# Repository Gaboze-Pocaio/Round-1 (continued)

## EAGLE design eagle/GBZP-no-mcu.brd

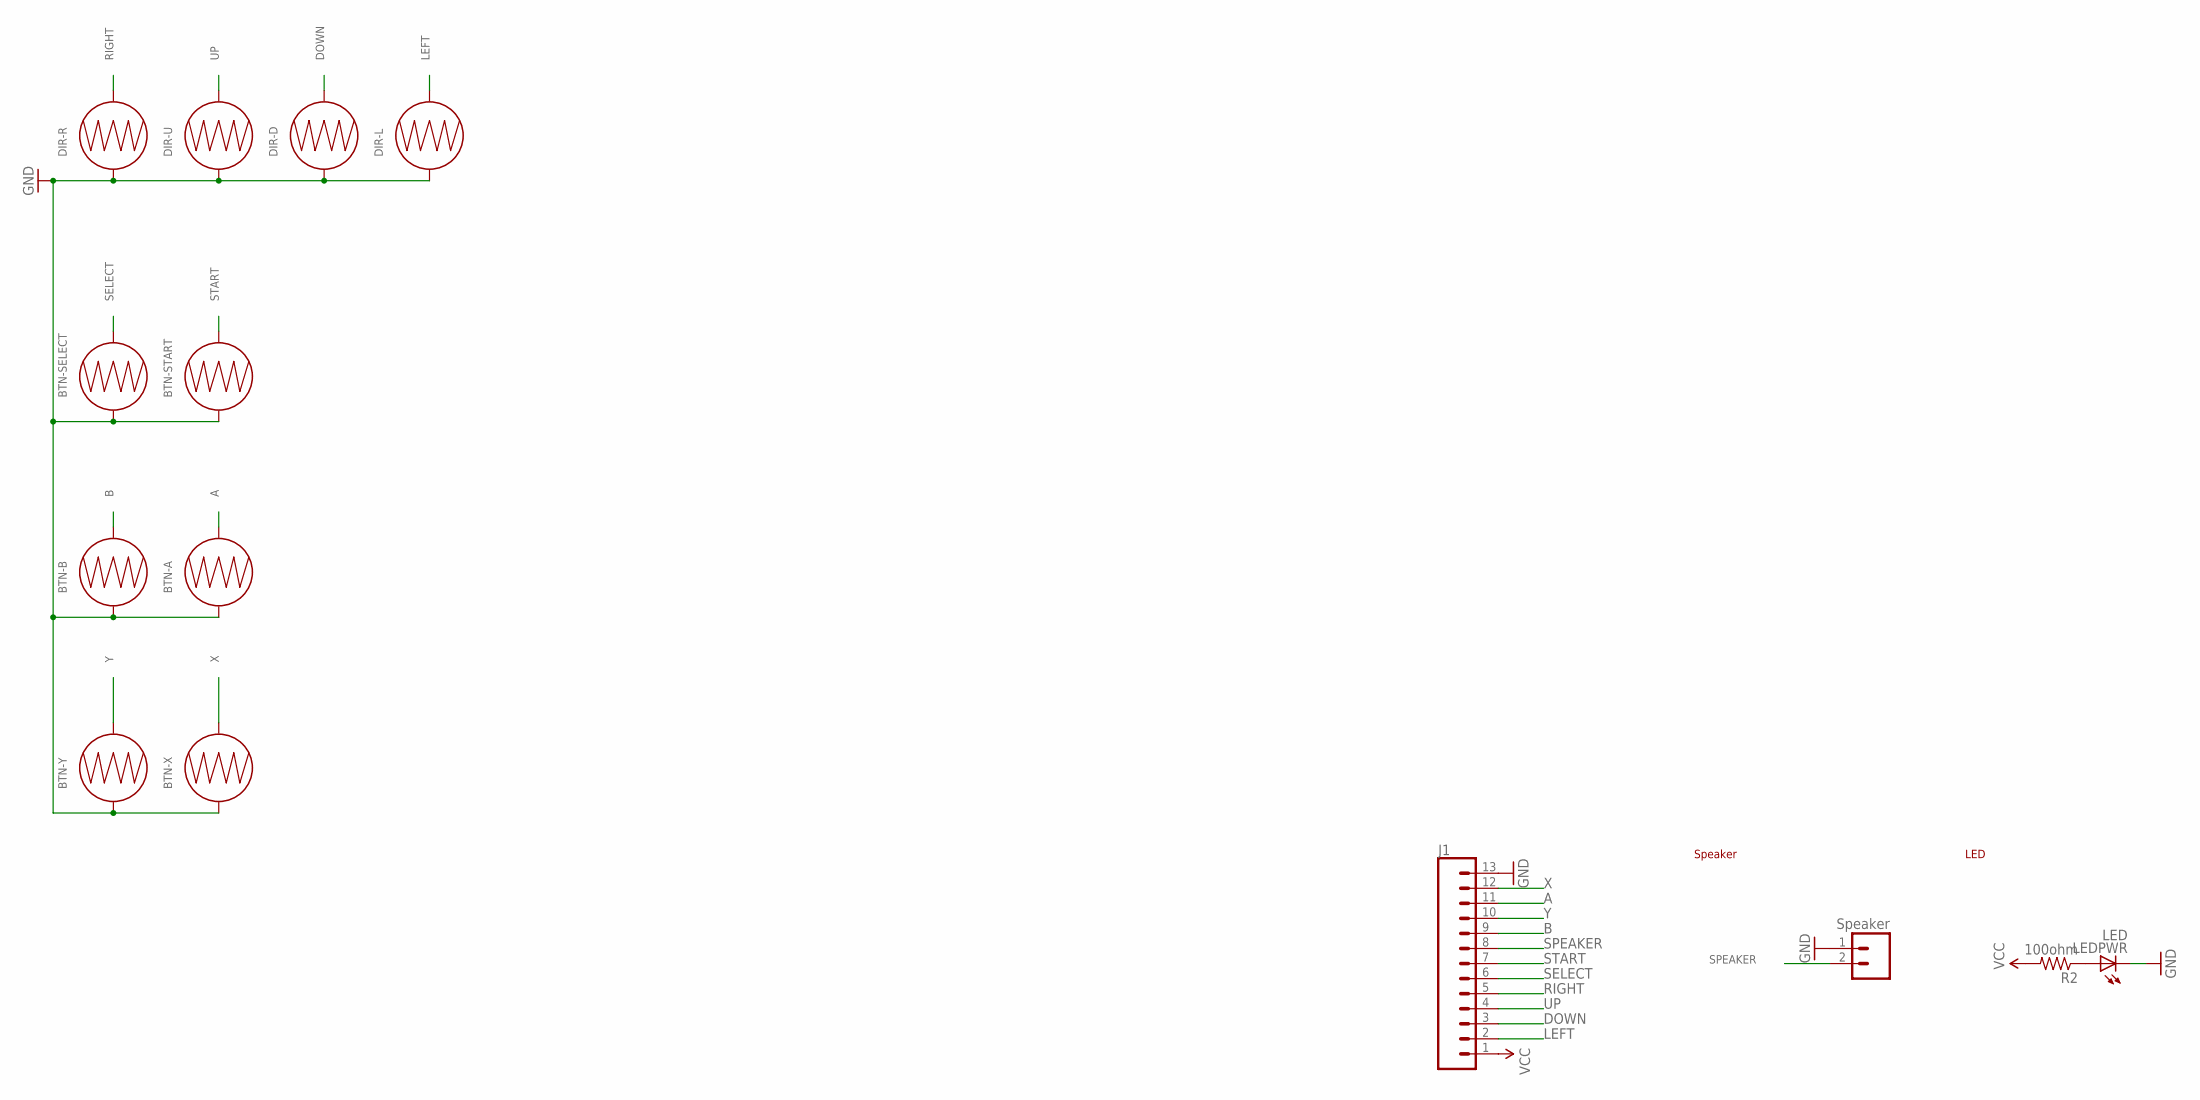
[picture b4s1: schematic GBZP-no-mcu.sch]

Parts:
BTN-A: BUTTON-CONDUCTIVESMD; BUTTON-CONDUCTIVE
BTN-B: BUTTON-CONDUCTIVESMD; BUTTON-CONDUCTIVE
BTN-SELECT: BUTTON-CONDUCTIVESMD; BUTTON-CONDUCTIVE
BTN-START: BUTTON-CONDUCTIVESMD; BUTTON-CONDUCTIVE
BTN-X: BUTTON-CONDUCTIVESMD; BUTTON-CONDUCTIVE
BTN-Y: BUTTON-CONDUCTIVESMD; BUTTON-CONDUCTIVE
DIR-D: BUTTON-CONDUCTIVESMD; BUTTON-CONDUCTIVE
DIR-L: BUTTON-CONDUCTIVESMD; BUTTON-CONDUCTIVE
DIR-R: BUTTON-CONDUCTIVESMD; BUTTON-CONDUCTIVE
DIR-U: BUTTON-CONDUCTIVESMD; BUTTON-CONDUCTIVE
J1: CONN_13; 1X13
JP2: Speaker; 1X02_NO_SILK
LEDPWR: LED; CHIPLED_0805
R2: 100ohm; R0805

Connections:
A: BTN-A.2, J1.11
B: BTN-B.2, J1.9
DOWN: DIR-D.2, J1.3
GND: BTN-A.1, BTN-B.1, BTN-SELECT.1, BTN-START.1, BTN-X.1, BTN-Y.1, DIR-D.1, DIR-L.1, DIR-R.1, DIR-U.1, J1.13, JP2.1, LEDPWR.C
LEFT: DIR-L.2, J1.2
unnamed: LEDPWR.A, R2.1
RIGHT: DIR-R.2, J1.5
SELECT: BTN-SELECT.2, J1.6
SPEAKER: J1.8, JP2.2
START: BTN-START.2, J1.7
UP: DIR-U.2, J1.4
VCC: J1.1, R2.2
X: BTN-X.2, J1.12
Y: BTN-Y.2, J1.10

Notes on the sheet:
LED
Speaker

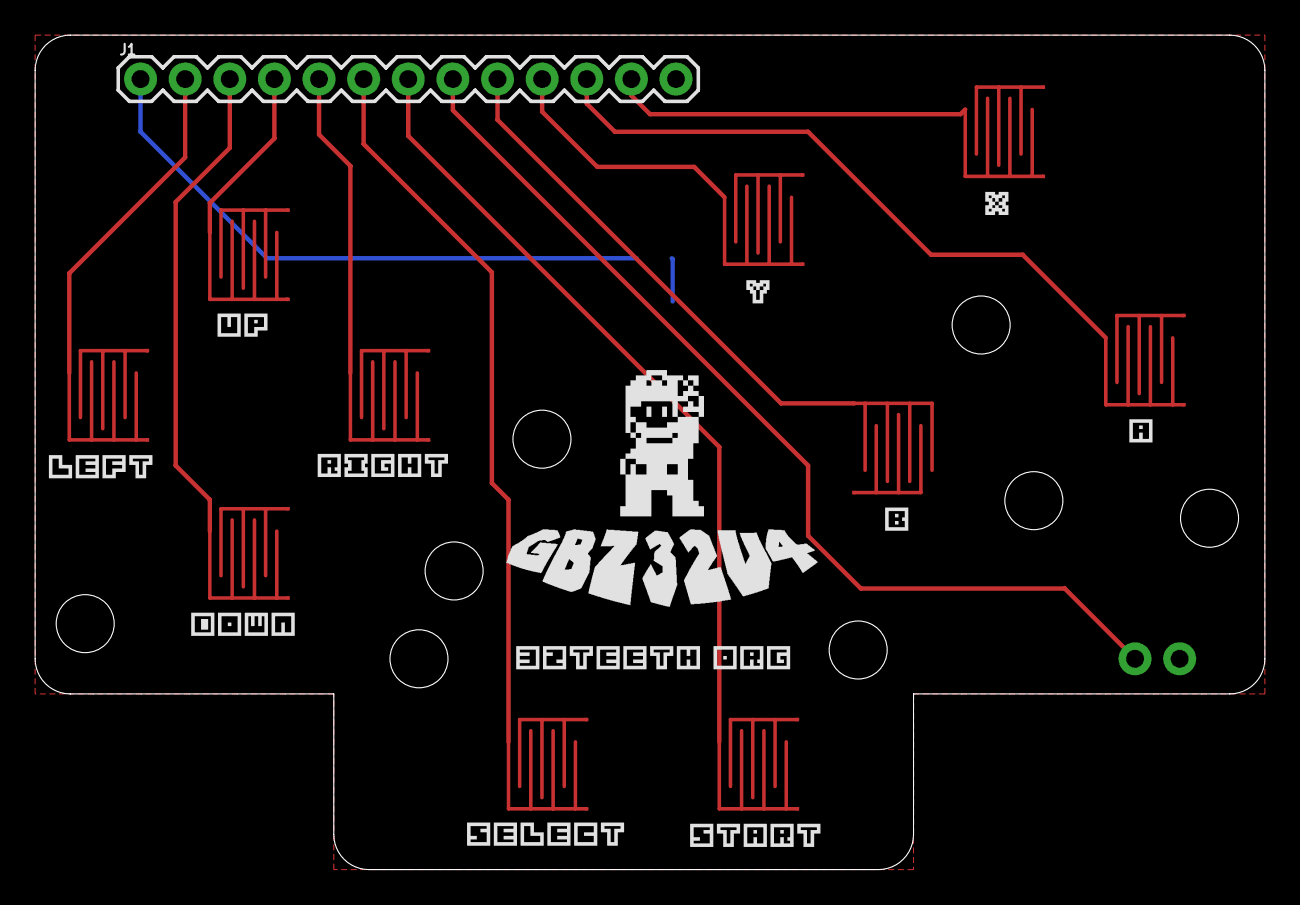
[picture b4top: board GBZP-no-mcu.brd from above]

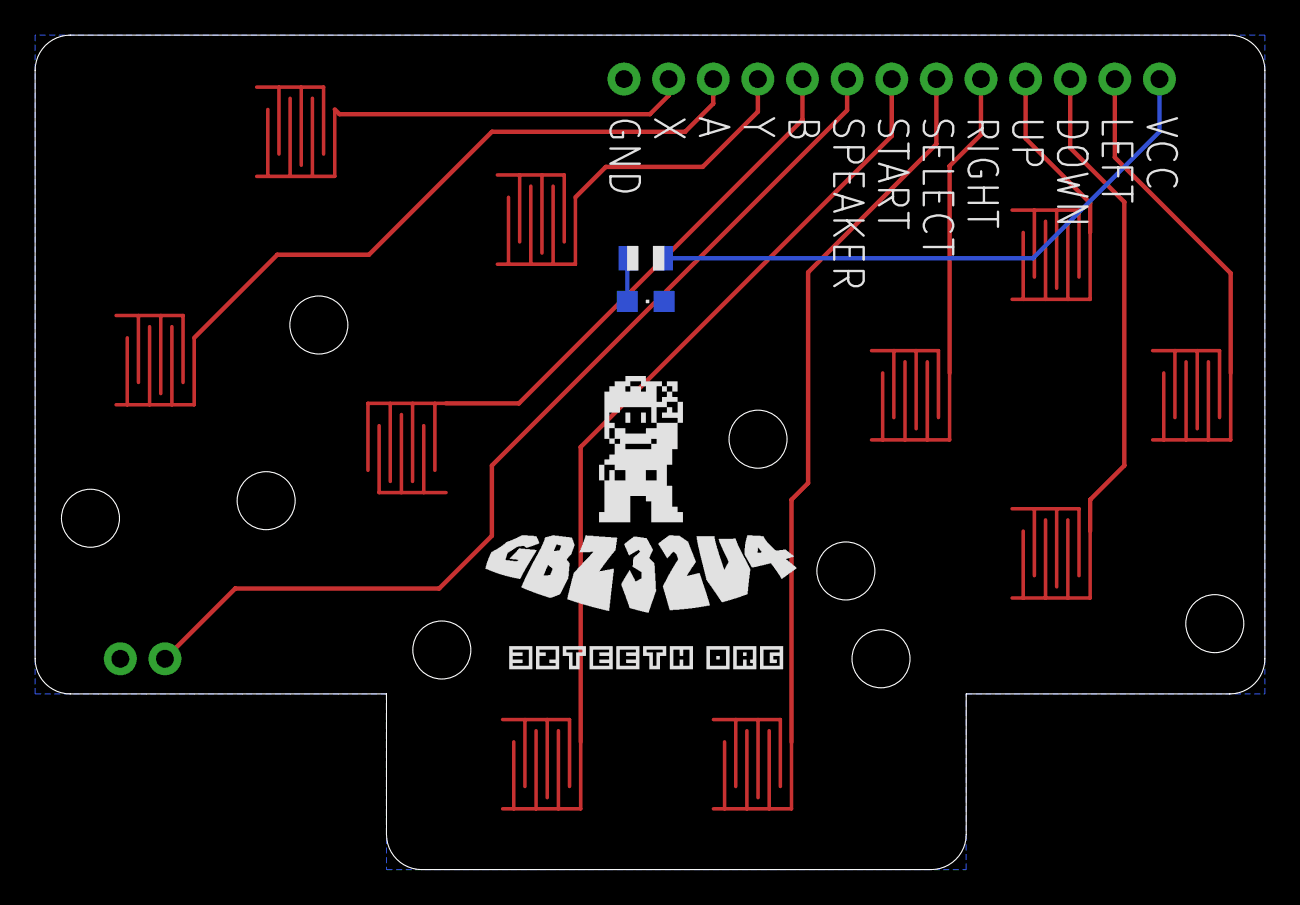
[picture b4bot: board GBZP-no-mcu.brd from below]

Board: 2 copper layers, 70.0 x 47.5 mm, 22 parts (2 on the bottom side), 14 nets.

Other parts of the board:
U$3, U$4, U$5, U$6, U$7, U$9, U$10, U$11: STAND-OFF

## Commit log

2017-03-16 Published Commit
2017-03-17 added no mcu version
2017-03-20 added reference and font
2017-03-31 new pinout to match GBZ project
2017-04-03 Mon Apr 3 10:04:51 EDT 2017 - added new pin mapping
2017-04-03 Mon Apr 3 10:13:43 EDT 2017 - added new pin mapping
2017-04-03 Mon Apr 3 10:14:23 EDT 2017 - added new pin mapping
2017-04-04 Tue Apr 4 07:14:17 EDT 2017
2017-04-04 Tue Apr 4 17:54:58 EDT 2017
2017-04-11 Added 3D models (stl files)
2017-04-11 Added 3D models
2017-08-09 Wed Aug 9 10:25:52 EDT 2017 new version of GBZP
2017-08-14 Mon Aug 14 17:07:33 EDT 2017 - Added Breakout to Silk Layer in PCB
2017-09-28 Thu 28 Sep 2017 18:31:30 EDT
2017-09-29 Fri Sep 29 08:38:18 EDT 2017 - cleaning schematics
2017-09-29 Fri 29 Sep 2017 10:20:31 EDT
2017-09-29 Fri 29 Sep 2017 15:06:16 EDT
2017-09-29 Fri 29 Sep 2017 19:00:00 EDT
2017-09-29 Fri 29 Sep 2017 19:00:14 EDT
2017-10-01 Sun Oct 1 16:53:47 EDT 2017
2017-10-01 Sun Oct 1 17:41:23 EDT 2017
2017-10-02 Sun Oct 1 21:02:41 EDT 2017
2017-10-02 Mon Oct 2 08:17:52 EDT 2017
2017-10-02 clean up
2017-10-03 Mon Oct 2 22:18:43 EDT 2017
2017-10-03 Mon Oct 2 23:35:09 EDT 2017
2017-10-06 Thu 5 Oct 2017 20:01:31 EDT
2017-10-06 Fri 6 Oct 2017 16:14:36 EDT
2017-10-06 Fri 6 Oct 2017 16:19:55 EDT
2017-10-06 Fri 6 Oct 2017 16:25:06 EDT
2017-10-11 New Silk and New Case files
2017-10-16 added LM4875
2017-10-17 headphones
2017-10-18 Tue Oct 17 23:18:40 EDT 2017
2017-10-18 Tue Oct 17 23:19:18 EDT 2017
2017-10-18 Wed Oct 18 00:38:32 EDT 2017
2017-10-27 Fri 27 Oct 2017 17:16:55 EDT
2017-10-30 Mon 30 Oct 2017 18:03:57 EDT
2017-10-31 Tue 31 Oct 2017 16:24:12 EDT
2017-11-06 Mon 6 Nov 2017 08:50:14 EST
2017-11-06 Mon 6 Nov 2017 16:41:18 EST
2017-11-11 Sat 11 Nov 2017 12:28:11 EST
2017-11-12 Sun Nov 12 12:23:45 EST 2017
2017-11-14 Tue 14 Nov 2017 17:21:21 EST
2017-11-21 Tue 21 Nov 2017 08:23:26 EST
2017-11-21 Tue 21 Nov 2017 14:22:23 EST
2017-11-21 Tue 21 Nov 2017 18:24:16 EST
2017-11-21 Tue 21 Nov 2017 18:40:45 EST
2017-11-22 Wed 22 Nov 2017 16:59:29 EST
2017-11-22 Wed 22 Nov 2017 17:04:44 EST
2017-11-23 Thu 23 Nov 2017 10:17:32 EST
2017-11-23 Thu 23 Nov 2017 16:37:40 EST
2017-11-29 Tue 28 Nov 2017 19:11:42 EST - ITS MACRO TIME
2017-12-11 Mon 11 Dec 2017 10:41:30 EST
2017-12-11 Mon 11 Dec 2017 15:35:34 EST
2017-12-11 Mon 11 Dec 2017 16:43:34 EST
2017-12-17 Sun 17 Dec 2017 11:46:58 EST
2017-12-20 Wed 20 Dec 2017 11:57:53 EST
2017-12-20 Wed 20 Dec 2017 11:58:10 EST
2017-12-22 Fri 22 Dec 2017 10:12:49 EST
2017-12-22 Fri 22 Dec 2017 11:04:23 EST
2017-12-28 Thu 28 Dec 2017 12:07:09 EST
2017-12-29 Fri 29 Dec 2017 10:38:17 EST
2017-12-30 Sat Dec 30 00:07:07 EST 2017
2017-12-30 Sat Dec 30 09:54:11 EST 2017
2018-01-02 Tue 2 Jan 2018 09:11:32 EST
2018-01-02 Tue 2 Jan 2018 16:23:20 EST
2018-01-02 Tue 2 Jan 2018 16:58:27 EST
2018-01-02 Tue 2 Jan 2018 16:58:39 EST
2018-01-03 Wed 3 Jan 2018 16:48:24 EST
2018-01-03 Wed 3 Jan 2018 16:48:57 EST
2018-01-03 Wed 3 Jan 2018 16:51:44 EST
2018-01-04 Thu Jan 4 01:14:42 EST 2018
2018-01-04 all traces ripped up and placement accurate
2018-01-04 routed main components and usb for charging
2018-01-12 Fri 12 Jan 2018 17:10:07 EST
2018-01-29 fixed 2.4" LCD position
2018-01-30 Tue Jan 30 17:53:42 EST 2018
2018-01-30 Tue Jan 30 18:48:27 EST 2018
2018-02-02 added retrogame.cfg
2018-02-08 Thu 8 Feb 2018 15:57:45 EST
2018-02-14 Wed 14 Feb 2018 12:35:03 EST
2018-02-21 Wed 21 Feb 2018 12:43:42 EST
2018-02-23 Fri 23 Feb 2018 09:16:37 EST
2018-02-26 Mon 26 Feb 2018 10:48:47 EST
2018-02-26 Mon 26 Feb 2018 17:32:14 EST
2018-02-26 Mon 26 Feb 2018 17:38:44 EST
2018-02-27 Tue 27 Feb 2018 16:38:24 EST
2018-02-28 Wed Feb 28 00:38:41 EST 2018 - added top silk
2018-02-28 Wed Feb 28 00:40:13 EST 2018 - added top silk
2018-02-28 Wed Feb 28 00:42:21 EST 2018 - added 3d model
2018-02-28 Wed Feb 28 00:44:10 EST 2018 - added 3d model
2018-02-28 Wed 28 Feb 2018 10:48:53 EST
2018-02-28 Wed 28 Feb 2018 10:49:42 EST
2018-02-28 Wed 28 Feb 2018 11:02:33 EST
2018-02-28 Wed 28 Feb 2018 12:18:39 EST
2018-03-06 renamed repository
2018-03-09 =Fri Mar 9 07:52:40 EST 2018
2018-03-10 Fri 9 Mar 2018 22:54:46 EST - initial commit for sharing
2018-03-22 Thu 22 Mar 2018 13:43:49 EDT
2018-03-22 Thu 22 Mar 2018 17:21:28 EDT
2018-03-22 Thu 22 Mar 2018 17:23:16 EDT
2018-03-22 Thu 22 Mar 2018 17:23:31 EDT
2018-03-22 Thu 22 Mar 2018 17:24:08 EDT
2018-04-05 README Link
2018-04-16 Mon 16 Apr 2018 10:01:08 EDT - Clean Up for Rebrand
2018-04-16 Mon 16 Apr 2018 10:06:31 EDT - Clean Up for Rebrand
2018-04-16 Mon 16 Apr 2018 10:07:00 EDT - Clean Up for Rebrand
2018-04-16 Mon 16 Apr 2018 10:07:17 EDT - Clean Up for Rebrand
2018-04-16 Mon 16 Apr 2018 10:07:52 EDT - Clean Up for Rebrand
2018-04-16 Mon 16 Apr 2018 10:19:39 EDT - Clean Up for Rebrand
2018-04-17 Tue 17 Apr 2018 16:29:39 EDT - Clean Up for Rebrand
2018-04-17 Tue 17 Apr 2018 16:31:36 EDT - Clean Up for Rebrand
2018-04-18 feat: Improved readability using CSV Rendering
2018-04-18 Wed 18 Apr 2018 10:22:51 EDT
2018-04-18 Wed 18 Apr 2018 11:40:42 EDT
2018-04-18 Wed 18 Apr 2018 15:35:03 EDT
2018-04-18 Wed 18 Apr 2018 15:38:02 EDT
2018-04-18 Wed 18 Apr 2018 16:16:52 EDT
2018-04-20 Fri 20 Apr 2018 10:16:35 EDT
2018-04-24 Tue 24 Apr 2018 11:37:34 EDT - Final Product Gerbers Uploaded and Renamed
2018-04-24 Tue 24 Apr 2018 18:52:09 EDT
2018-04-30 Mon 30 Apr 2018 06:26:32 EDT - rotate display
2018-05-02 Tue 1 May 2018 20:50:57 EDT - added overscan for 2.4 inch screen
2018-05-03 Thu 3 May 2018 12:15:34 EDT - Added Components in README
2018-05-03 Thu 3 May 2018 12:33:28 EDT - Added Components in README
2018-05-03 Thu 3 May 2018 12:40:03 EDT - Added Components in README
2018-05-03 Thu 3 May 2018 12:40:38 EDT - Added Components in README
2018-05-03 Thu 3 May 2018 12:43:31 EDT - Clean and Sync with Dev
2018-05-03 Thu 3 May 2018 12:51:01 EDT - Clean and Sync with Dev
2018-05-03 Thu 3 May 2018 12:51:25 EDT - Clean and Sync with Dev
2018-05-07 Mon 7 May 2018 10:35:34 EDT - added theme folder
2018-05-14 Mon 14 May 2018 09:12:45 EDT - added theme folder
2018-05-15 Tue 15 May 2018 10:58:43 EDT - update BOM
2018-05-15 Tue 15 May 2018 11:01:23 EDT - update gerbers
2018-05-30 Wed 30 May 2018 10:20:05 EDT
2018-06-03 Sun 3 Jun 2018 09:47:55 EDT
2018-06-11 Mon 11 Jun 2018 17:00:27 EDT
2018-06-15 Fri 15 Jun 2018 16:23:04 EDT
2018-06-15 Fri 15 Jun 2018 16:23:22 EDT
2018-06-15 Fri 15 Jun 2018 16:23:49 EDT
2018-06-27 Wed 27 Jun 2018 09:32:48 EDT
2018-06-27 Wed 27 Jun 2018 09:56:59 EDT
2018-06-27 Wed 27 Jun 2018 14:44:33 EDT
2018-06-27 Wed 27 Jun 2018 14:45:09 EDT
2018-06-27 Wed 27 Jun 2018 14:47:23 EDT
2018-06-27 Wed 27 Jun 2018 14:50:57 EDT
2018-06-27 Wed 27 Jun 2018 14:51:48 EDT
2018-06-29 Fri 29 Jun 2018 10:04:19 EDT
2018-06-29 Fri 29 Jun 2018 10:06:18 EDT
2018-06-29 Fri 29 Jun 2018 10:17:32 EDT
2018-07-06 Fri 6 Jul 2018 06:25:10 EDT
2018-07-06 Fri 6 Jul 2018 16:18:57 EDT - added libraries
2018-07-06 Fri 6 Jul 2018 16:19:57 EDT - updated Layout
2018-07-06 Fri 6 Jul 2018 16:31:20 EDT - updated Layout
2018-07-06 Fri 6 Jul 2018 16:41:46 EDT - updated Layout
2018-07-08 Sun 8 Jul 2018 18:12:22 EDT
2018-07-09 Sun 8 Jul 2018 20:49:34 EDT
2018-07-09 Mon 9 Jul 2018 07:03:52 EDT - added DISCLAIMER.md for gerbers
2018-07-09 Mon 9 Jul 2018 07:06:11 EDT - updated layour eagle files
2018-07-12 Wed 11 Jul 2018 21:18:07 EDT - updated layour eagle files
2018-07-12 Thu 12 Jul 2018 07:06:00 EDT - updated layour eagle files
2018-07-12 Thu 12 Jul 2018 12:41:02 EDT - general cleanup
2018-07-13 Fri 13 Jul 2018 07:20:31 EDT - updated layout eagle files with new buttons
2018-07-17 Tue 17 Jul 2018 06:00:31 EDT - links
2018-07-23 Mon 23 Jul 2018 16:21:42 EDT - added button configuration
2018-07-23 Mon 23 Jul 2018 16:32:51 EDT - added button configuration
2018-07-24 Tue 24 Jul 2018 16:16:34 EDT - readme edit
2018-07-24 Tue 24 Jul 2018 16:19:20 EDT - general cleanup
2018-07-24 Tue 24 Jul 2018 16:20:39 EDT - general cleanup
2018-07-24 Tue 24 Jul 2018 16:21:24 EDT - general cleanup
2018-07-26 Thu 26 Jul 2018 06:20:51 EDT - K0601N0 library updated
2018-07-26 Thu 26 Jul 2018 06:38:09 EDT - removed /docs folder
2018-07-26 Thu 26 Jul 2018 06:39:13 EDT - removed /docs folder
2018-07-26 Thu 26 Jul 2018 11:33:07 EDT
2018-07-27 Fri 27 Jul 2018 16:50:06 EDT - added Button Membrane.md
2018-07-27 Fri 27 Jul 2018 16:51:31 EDT - fixed TOC in INSTALL.md
2018-07-27 Fri 27 Jul 2018 17:29:48 EDT - Library Clean Up
2018-07-27 Fri 27 Jul 2018 18:58:13 EDT - Library Clean Up
2018-08-07 Tue 7 Aug 2018 00:11:16 EDT - update library
2018-08-07 added
2018-08-08 Wed 8 Aug 2018 12:18:13 EDT - Library Clean Up
2018-08-09 Thu 9 Aug 2018 09:28:51 EDT - Released PCB (SCH/BRD/Gerbers/ZIP) for Official Release to Public
2018-08-09 Thu 9 Aug 2018 09:29:46 EDT - Released PCB (SCH/BRD/Gerbers/ZIP) for Official Release to Public
2018-08-09 Thu 9 Aug 2018 09:31:27 EDT - Released PCB (SCH/BRD/Gerbers/ZIP) for Official Release to Public
2018-08-09 Thu 9 Aug 2018 09:33:37 EDT - Updated README.md
2018-08-09 Thu 9 Aug 2018 09:37:09 EDT - Fixed Link in README.md
2018-08-17 Fri 17 Aug 2018 12:44:01 EDT - lbr folder cleanup
2018-08-18 added 2.6 gerber files and zip
2018-08-20 Mon 20 Aug 2018 11:02:57 EDT
2018-08-24 Fri 24 Aug 2018 14:03:31 EDT update all library files
2018-08-30 Thu 30 Aug 2018 11:15:03 EDT update all library files
2018-08-30 Thu 30 Aug 2018 11:17:51 EDT update all library files
2018-08-30 Thu 30 Aug 2018 11:22:50 EDT update all library files
2018-08-30 Thu 30 Aug 2018 11:23:21 EDT update all library files
2018-08-30 Thu 30 Aug 2018 11:24:09 EDT update all library files
2018-08-30 Thu 30 Aug 2018 11:24:43 EDT typo
2018-08-31 Fri 31 Aug 2018 14:38:03 EDT
2018-09-06 Thu 6 Sep 2018 12:15:06 EDT added gerbers for extension boards
2018-09-13 Thu 13 Sep 2018 10:30:32 EDT updated BOM
2018-09-13 Thu 13 Sep 2018 10:31:57 EDT updated BOM
2018-09-18 Tue 18 Sep 2018 17:13:24 EDT - added .stl file for 3d printing cartridge shell
2018-09-18 Tue 18 Sep 2018 17:17:02 EDT - added .stl file for 3d printing cartridge shell
2018-09-19 Wed 19 Sep 2018 13:57:21 EDT - added 2.6" upgrrade
2018-09-19 Wed 19 Sep 2018 14:04:33 EDT - added 2.6" upgrade
2018-09-19 Wed 19 Sep 2018 14:05:32 EDT - added 2.6" upgrade
2018-09-19 Wed 19 Sep 2018 14:06:58 EDT - added 2.6" upgrade
2018-09-19 Wed 19 Sep 2018 14:11:41 EDT - added 2.6" upgrade
2018-09-26 Wed 26 Sep 2018 05:51:11 EDT
2018-10-15 Mon 15 Oct 2018 17:02:15 EDT
2018-10-15 Mon 15 Oct 2018 17:04:18 EDT
2018-10-15 Mon 15 Oct 2018 17:10:01 EDT - Dd link to readme
2018-10-15 Mon 15 Oct 2018 17:10:39 EDT - added link to readme
2018-11-23 Fri 23 Nov 2018 13:27:56 EST - resotred images
2018-11-23 Fri 23 Nov 2018 13:29:44 EST - resotred images
2018-11-23 Fri 23 Nov 2018 13:30:32 EST - resotred images
